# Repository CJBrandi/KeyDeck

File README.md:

# KeyDeck
The KeyDeck is a custom designed macropad that is semi-based on the [Hackpad]([url](https://hackpad.hackclub.com)) tutorial. I used KiCad to create a custom schematic and pcb for my own macropad, then I used Onshape to cad everything from the case to the full assembly of the KeyDeck, I researched the parts from many different sellers and decided on the best ones, and wrote some alpha firmware for the main controller. I made this project because I always have wanted to make a Hack Club project but never found the right one for me. I can say that I originally just wanted to make a simple HackPad but now this has evolved into something more, something that helped me learn many useful software and engineering skills too along the way. This project isn't very complex or anything extremely special, but i'm proud of it because of the skills I learned.

# CAD Link:
https://cad.onshape.com/documents/f0da09f9133df872021c7bb6/w/39fd902933bfae87f6640d91/e/d6283e9f59527cd2ccb38ed5  
(A bit messy, but serves it's job)
# KeyDeck Renders:

Corner Shot

Side View

Top Down

# KeyDeck CAD Images:

Top Angle

Top Down

# KeyDeck PCB

PCB Schematic

PCB Cad With A Few Components

# KeyDeck BOM

| Name:                                     | Description:                                                                                                                                                                                                                                                                                                                                                                                                                       | Quantity: | Final Price: | Link: |
| ----------------------------------------- | ---------------------------------------------------------------------------------------------------------------------------------------------------------------------------------------------------------------------------------------------------------------------------------------------------------------------------------------------------------------------------------------------------------------------------------- | --------- | ------------ | ----- |
| Cherry MX Red Switches                    | Keyswitches to be used on the KeyDeck. These are not official but are price optimized from Aliexpress. Should serve the same puurpose just fine. I have to have the full price because the $0.99 discount is the LEDs, which is more expensive overall. Tax and Shipping for both LEDs and Switches included in the LEDs price because the actual product was cheaper. Decided to get a few extra incase I break any in assembly.  | 20        | $8.74        | [AliExpress](https://www.aliexpress.us/item/3256806069646359.html?spm=a2g0o.productlist.main.2.724a3474MZWkEA&algo_pvid=737d6045-fe2a-482a-ba36-cc2cdf85aea5&algo_exp_id=737d6045-fe2a-482a-ba36-cc2cdf85aea5-1&pdp_ext_f=%7B"order"%3A"1022"%2C"eval"%3A"1"%7D&pdp_npi=4%40dis%21USD%215.99%210.99%21%21%2143.01%217.14%21%402103244817542682999465243e2fa1%2112000036489552472%21sea%21US%216279080118%21ABX&curPageLogUid=tzxadgPFfUvE&utparam-url=scene%3Asearch%7Cquery_from%3A)  |
| KeyDeck PCB                               | PCB for the project. Had to order the minimum quantity which was 5. Coupon for $6 applied to make it extra cheap.                                                                                                                                                                                                                                                                                                                  | 5         | $3.50        | N/A   |
| Seeed Studio RP2040 XIAO                  | The main controller for the KeyDeck. Might be Backordered but that's alright. Using the pre-soldered version as I decided on manual assembly.                                                                                                                                                                                                                                                                                      | 1         | $13.76       | [Seeed Studio](https://www.seeedstudio.com/Seeed-Studio-XIAO-RP2040-Pre-Soldered-p-6333.html)  |
| SK6812 (Neopixel) LEDs                    | LEDs for the KeyDeck PCB. Minimum Quantity I could find was 100. Discount is applied on this one to make it $0.99 instead of the switches because this one is more expensive overall. Tax and Shipping for both Switches and LEDs included in this price.                                                                                                                                                                          | 100       | $4.31        | [AliExpress](https://www.aliexpress.us/item/3256807802380183.html?spm=a2g0o.productlist.main.3.3f24sYiDsYiDPe&algo_pvid=6ad03e82-cb50-4483-96eb-f1ae26d5de71&algo_exp_id=6ad03e82-cb50-4483-96eb-f1ae26d5de71-2&pdp_ext_f=%7B"order"%3A"15"%2C"eval"%3A"1"%7D&pdp_npi=4%40dis%21USD%2114.04%210.99%21%21%21100.82%217.11%21%40210313e917542746935784900eafd9%2112000043173268003%21sea%21US%216279080118%21ABX&curPageLogUid=ol3pGnDxLFVO&utparam-url=scene%3Asearch%7Cquery_from%3A)  |
| KeyDeck Case                              | This includes the base/body + lid. This case was designed to be 3D-Printed. I have a 3D-Printer and will be manufacturing all parts of this type myself.                                                                                                                                                                                                                                                                           | 1         | None         | N/A   |
| Keycaps                                   | The current keycaps on the cad are fine. I will 3D-Print these myself, removing the cost. In the future, I plan to make custom keycaps that are multi-color and have different logos on them to correspond to different shortcuts that they indicate. For now, stock keycaps are fine.                                                                                                                                             | 8         | None         | N/A   |
| 8-32 0.25in. Hex Drive Button Head Screws | The screws to be used to assemble the KeyDeck case. I have some, so no cost.                                                                                                                                                                                                                                                                                                                                                       | 4         | None         | [McMaster Carr](https://www.mcmaster.com/97763a176/)  |
| Total Cost:                               |                                                                                                                                                                                                                                                                                                                                                                                                                                    |           | $30.31       |       |

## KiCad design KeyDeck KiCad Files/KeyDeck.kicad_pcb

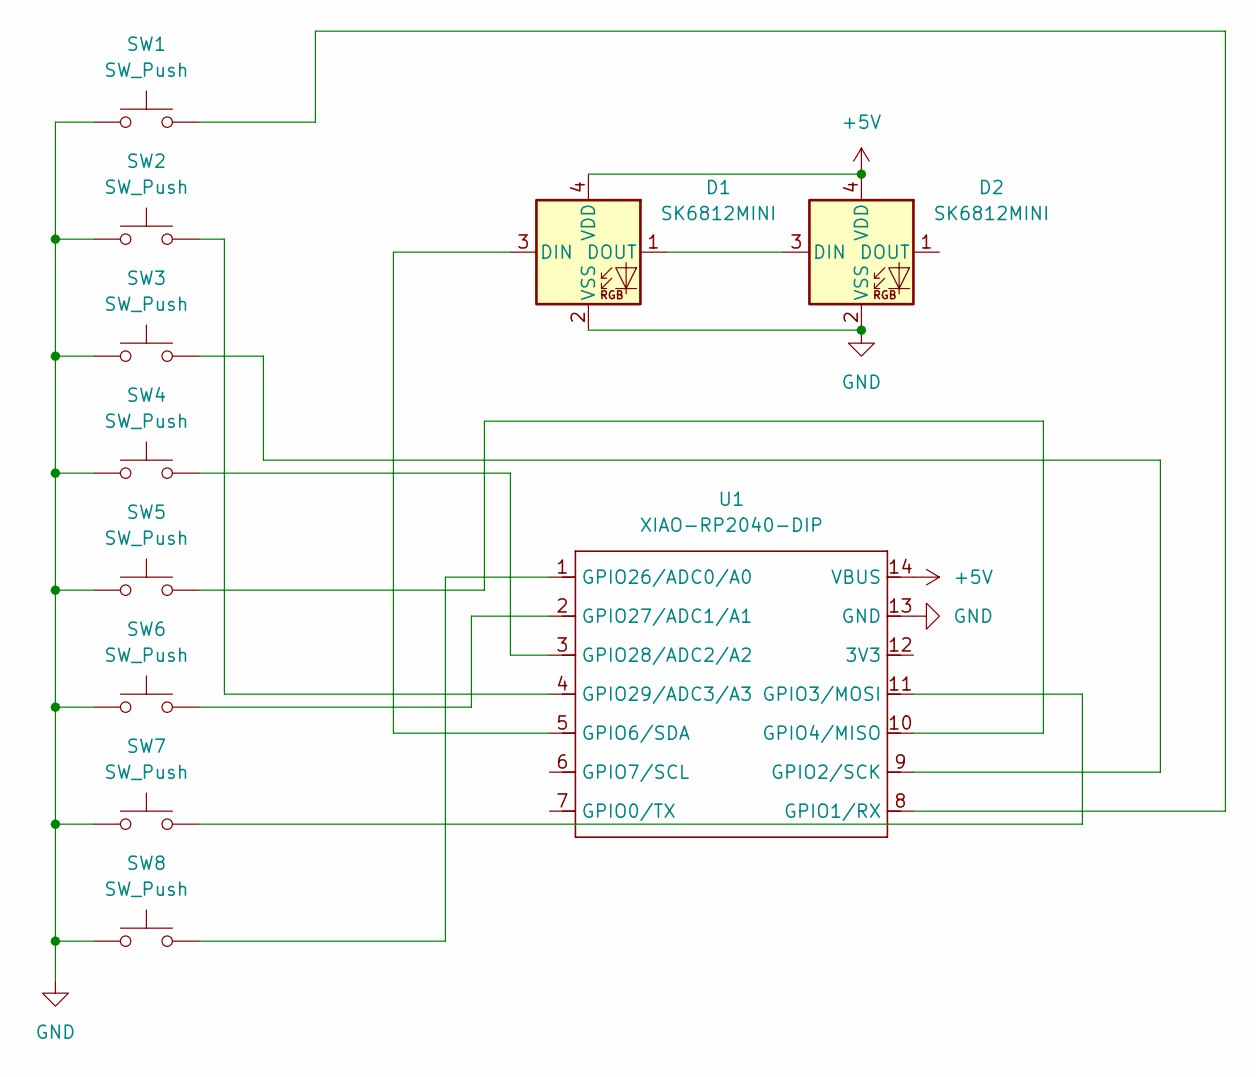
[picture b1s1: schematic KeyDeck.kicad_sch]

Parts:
D1, D2: SK6812MINI; LED_SK6812MINI_PLCC4_3.5x3.5mm_P1.75mm
SW1, SW2, SW3, SW4, SW5, SW6, SW7, SW8: SW_Push; SW_Cherry_MX_1.00u_PCB
U1: XIAO-RP2040-DIP; XIAO-RP2350-DIP

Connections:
+5V: D1.4 (VDD), D2.4 (VDD), U1.14 (VBUS)
GND: D1.2 (VSS), D2.2 (VSS), SW1.1, SW2.1, SW3.1, SW4.1, SW5.1, SW6.1, SW7.1, SW8.1, U1.13 (GND)
unnamed: D1.3 (DIN), U1.5 (GPIO6/SDA)
unnamed: D1.1 (DOUT), D2.3 (DIN)
unnamed: SW1.2, U1.8 (GPIO1/RX)
unnamed: SW3.2, U1.9 (GPIO2/SCK)
unnamed: SW7.2, U1.11 (GPIO3/MOSI)
unnamed: SW5.2, U1.10 (GPIO4/MISO)
unnamed: SW8.2, U1.1 (GPIO26/ADC0/A0)
unnamed: SW6.2, U1.2 (GPIO27/ADC1/A1)
unnamed: SW4.2, U1.3 (GPIO28/ADC2/A2)
unnamed: SW2.2, U1.4 (GPIO29/ADC3/A3)

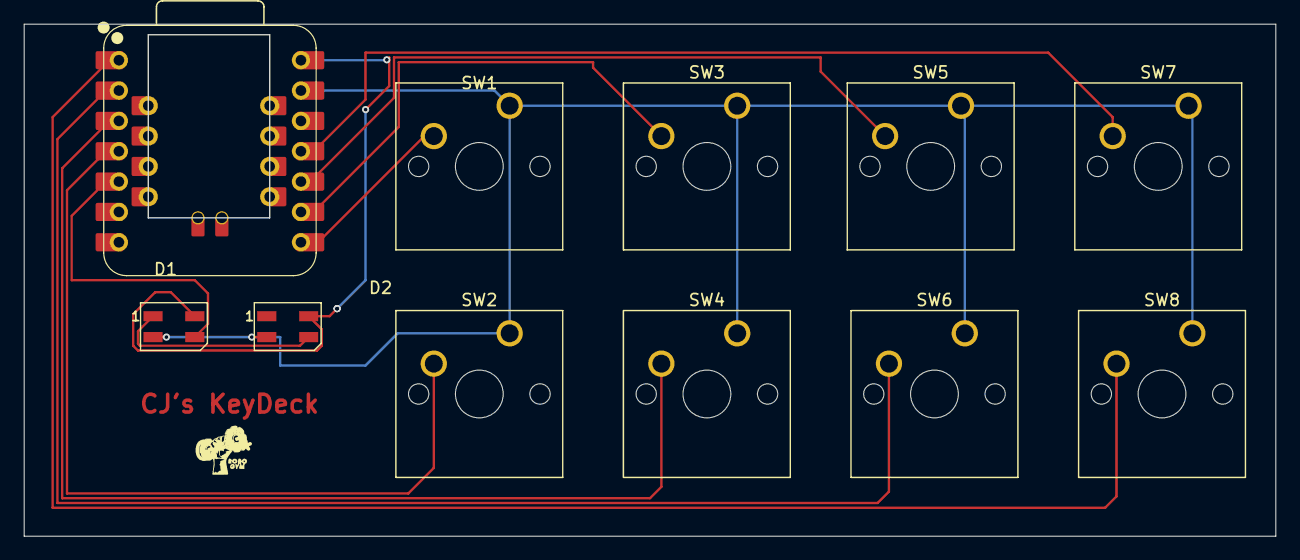
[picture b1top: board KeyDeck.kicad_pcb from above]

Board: 2 copper layers, 104.7 x 42.8 mm, 11 parts (0 on the bottom side), 12 nets.

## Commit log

2025-08-03 Update Journal.md for day 4
2025-08-04 Update Journal.md to show time spent per day.
2025-08-04 Update Journal.md for day 5
2025-08-05 Update Journal.md for day 6
2025-08-05 Update README.md with renders
2025-08-06 Update README.md to fulfill project guidelines.
2025-08-06 Fixed BOM
2025-08-06 Update Journal.md for day 7
2025-08-06 Add BOM Files.
2025-08-07 KiCad Folder
2025-08-07 rename folder
2025-08-08 Update README.md formatting and add onshape link
2025-08-08 Create ligma
2025-08-08 Rename ligma to CAD/ligma
2025-08-08 Add keydeck step assembly
2025-08-08 keydeck firmware addition
    This is a very alpha test version without any macros or anything else (like LEDs which I plan to add support to in the future) to just test if the assembled KeyDeck works.
2025-08-08 Rename gbr.zip to KeyDeck_Gerber.zip
2025-08-08 Update Journal.md for day 8
2025-08-08 Update README.md without soldering stipend to hopefully make the project eligible for grounded.
